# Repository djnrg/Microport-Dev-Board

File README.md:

# Microport-Dev-Board
Microport development board fot following microcontrollers:
* SAM D21
* PIC18F21

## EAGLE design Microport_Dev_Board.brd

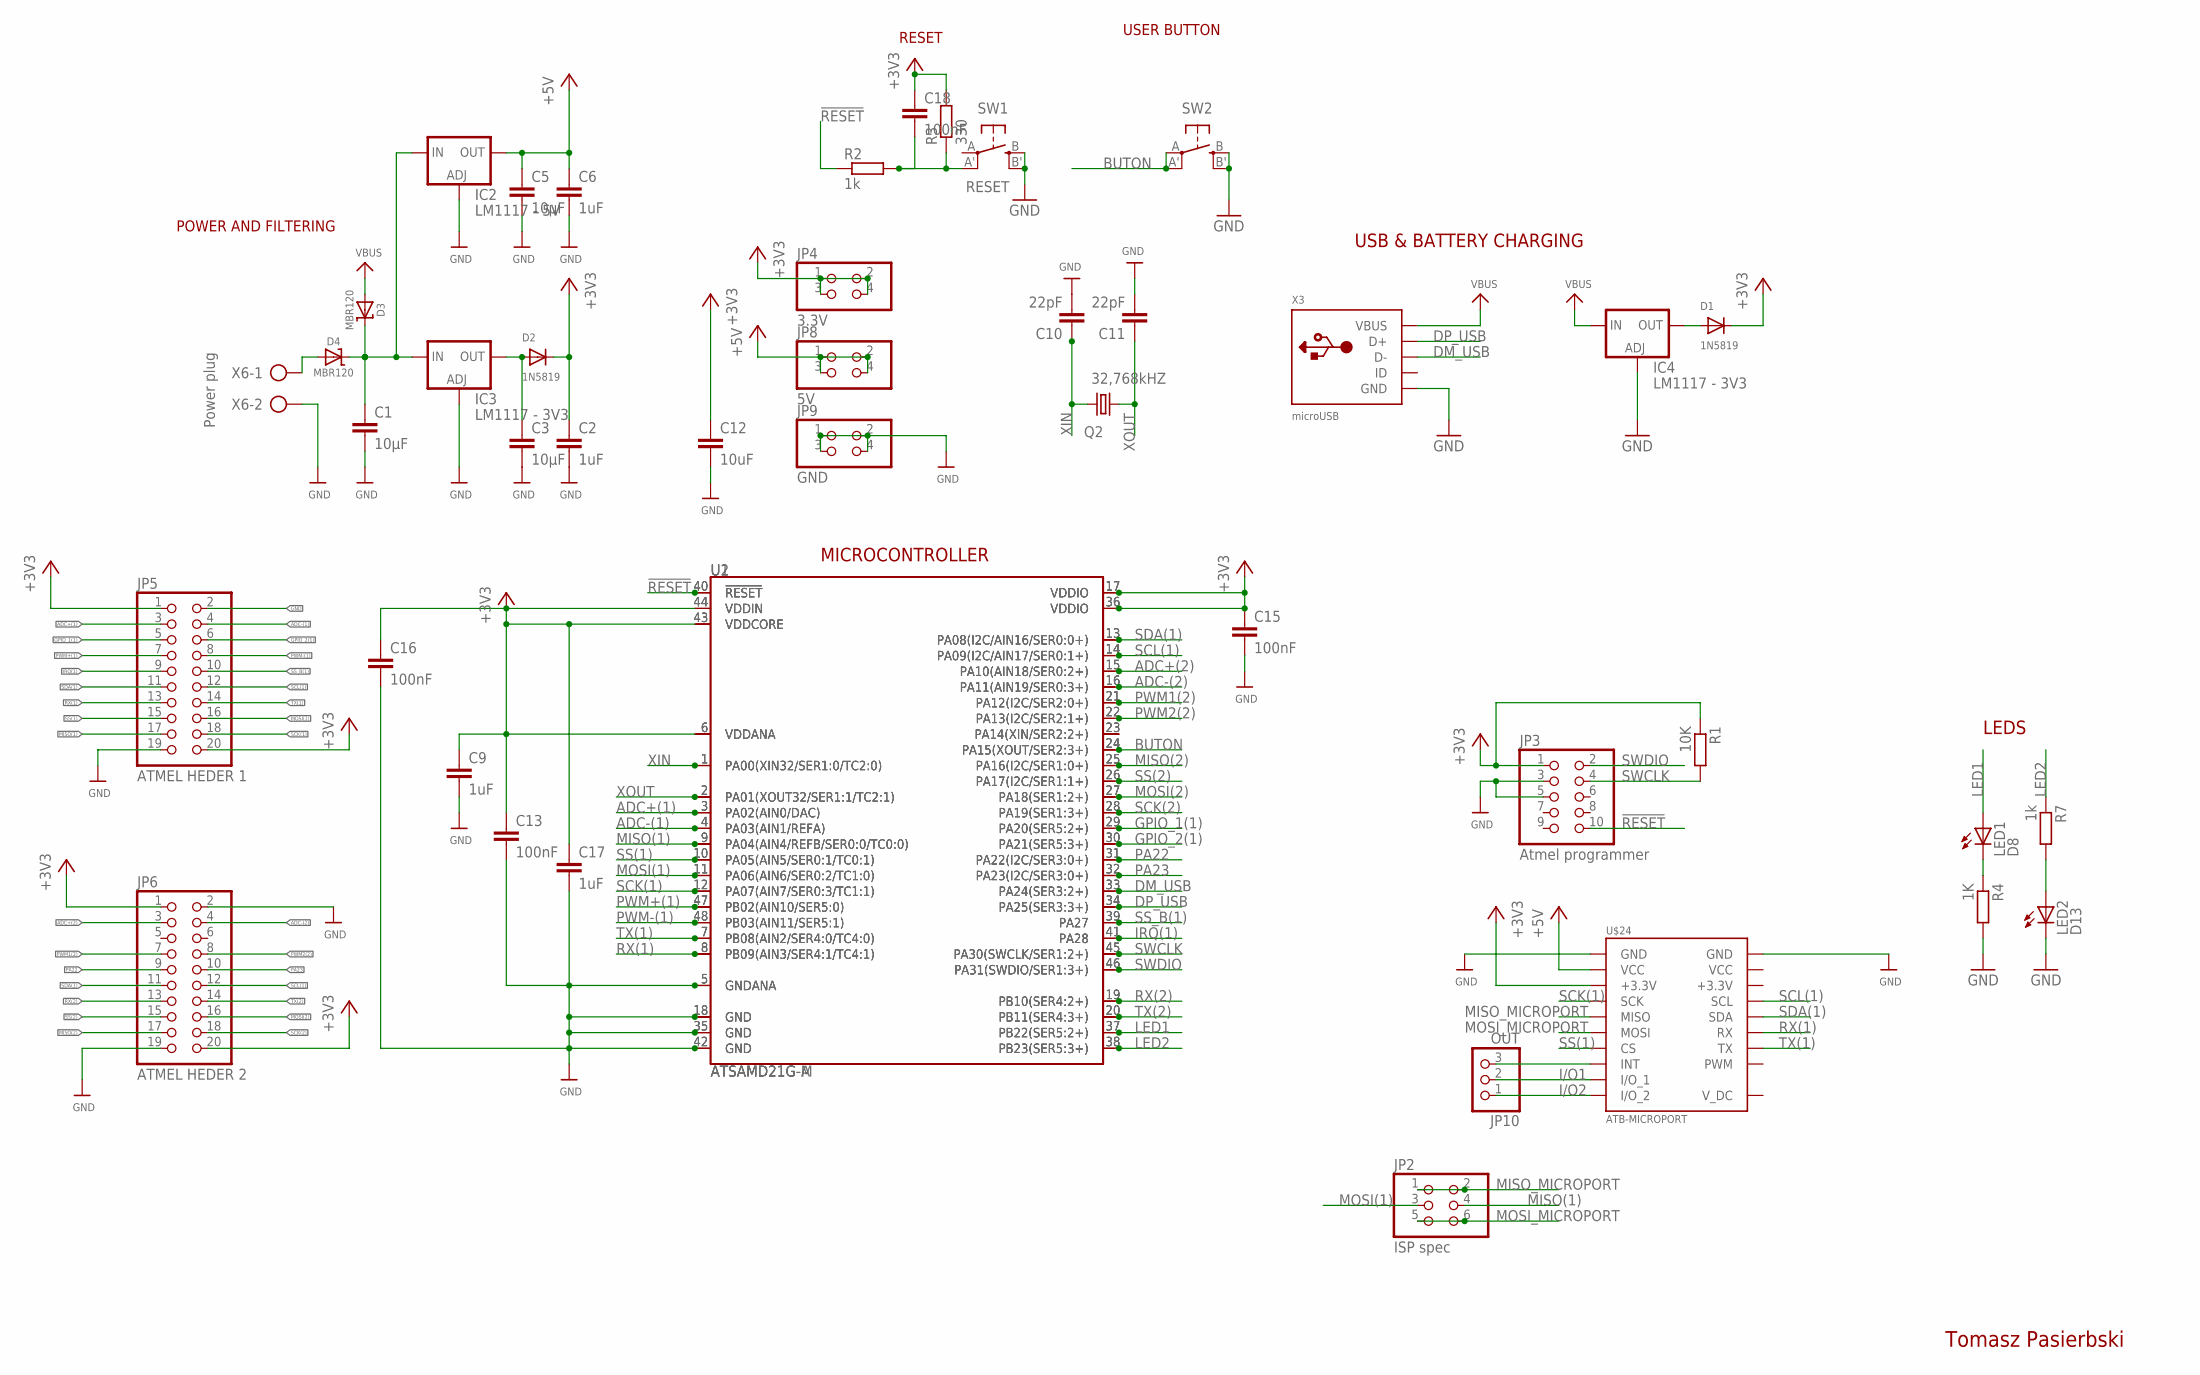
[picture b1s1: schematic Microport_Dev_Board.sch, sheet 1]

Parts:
C1, C3, C5: 10µF; C1206
C2, C6, C9, C17: 1uF; C1206
C10, C11: 22pF; C1206
C12: 10uF; C1206
C13, C15, C16, C18: 100nF; C1206
D1, D2: 1N5819; SOD-523
D3, D4: MBR120; SOD-123
IC2: LM1117 - 5V; SOT223
IC3, IC4: LM1117 - 3V3; SOT223
JP2: ISP spec; 2X03
JP3: Atmel programmer; 2X05
JP4: 3.3V; 2X02
JP5: ATMEL HEDER 1; 2X10
JP6: ATMEL HEDER 2; 2X10
JP8: 5V; 2X02
JP9: GND; 2X02
JP10: OUT; 1X03
LED1: D8; 1206
LED2: D13; 1206
Q2: 32,768kHZ; HC49UP
R1: 10K; M1206
R2: 1k; R1206
R3: 330; R1206
R4: 1K; M1206
R7: 1k; M1206
SW1: RESET; EVQ-Q2
SW2: USER BUTTON; EVQ-Q2
U1: ATSAMD21G-M; QFN-48
U2: ATSAMD21G-A; TQFP-48
U$24: ATB-MICROPORT
X3: microUSB; USB-MINIB
X6: Power plug; AK300/2

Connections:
!RESET: JP3.10, R2.1, U1.40 (!RESET!), U2.40 (!RESET!); also elsewhere on the board
+3.3V: U$24.P$17 (+3.3V)
+3V3: C2.1, C9.1, C12.1, C13.1, C15.1, C16.1, C17.1, C18.1, D1.K (C), D2.K (C), JP3.1, JP4.1, JP4.2, JP4.3, JP4.4, JP5.1, JP5.20, JP6.1, JP6.20, R1.1, R3.2, U1.17 (VDDIO), U1.36 (VDDIO), U2.6 (VDDANA), U2.17 (VDDIO), U2.36 (VDDIO), U2.43 (VDDCORE), U2.44 (VDDIN), U$24.P$3 (+3.3V); also elsewhere on the board
+5V: C5.1, C6.1, IC2.4 (OUT), JP8.1, JP8.2, JP8.3, JP8.4, U$24.P$2 (VCC); also elsewhere on the board
ADC+(1): JP5.3, U1.3 (PA02(AIN0/DAC)), U2.3 (PA02(AIN0/DAC))
ADC+(2): JP6.3, U1.15 (PA10(AIN18/SER0:2+)), U2.15 (PA10(AIN18/SER0:2+))
ADC-(1): JP5.4, U1.4 (PA03(AIN1/REFA)), U2.4 (PA03(AIN1/REFA))
ADC-(2): JP6.4, U1.16 (PA11(AIN19/SER0:3+)), U2.16 (PA11(AIN19/SER0:3+))
BUTON: SW2.A, SW2.A' (P1), U1.24 (PA15(XOUT/SER2:3+)), U2.24 (PA15(XOUT/SER2:3+))
DM_USB: U1.33 (PA24(SER3:2+)), U2.33 (PA24(SER3:2+)), X3.D-; also elsewhere on the board
DP_USB: U1.34 (PA25(SER3:3+)), U2.34 (PA25(SER3:3+)), X3.D+; also elsewhere on the board
GND: C1.2, C2.2, C3.2, C5.2, C6.2, C9.2, C10.2, C11.2, C12.2, C13.2, C15.2, C16.2, C17.2, IC2.1 (ADJ), IC3.1 (ADJ), IC4.1 (ADJ), JP3.3, JP3.5, JP5.2, JP5.19, JP6.2, JP6.19, JP9.1, JP9.2, JP9.3, JP9.4, LED2.C, R4.2, SW1.B (S), SW1.B' (S1), SW2.B (S), SW2.B' (S1), U1.5 (GNDANA), U1.18 (GND), U1.35 (GND), U1.42 (GND), U2.5 (GNDANA), U2.18 (GND), U2.35 (GND), U2.42 (GND), U$24.P$1 (GND), U$24.P$19 (GND), X3.GND, X6.2; also elsewhere on the board
GPIO_1(1): JP5.5, U1.29 (PA20(SER5:2+)), U2.29 (PA20(SER5:2+))
GPIO_2(1): JP5.6, U1.30 (PA21(SER5:3+)), U2.30 (PA21(SER5:3+))
I/O1: JP10.2, U$24.P$9 (I/O_1)
I/O2: JP10.1, U$24.P$10 (I/O_2)
IRQ(1): JP5.9, U1.41 (PA28), U2.41 (PA28)
LED1: LED1.A, U1.37 (PB22(SER5:2+)), U2.37 (PB22(SER5:2+))
LED2: R7.1, U1.38 (PB23(SER5:3+)), U2.38 (PB23(SER5:3+))
MISO(1): JP2.4, JP5.17, U1.9 (PA04(AIN4/REFB/SER0:0/TC0:0)), U2.9 (PA04(AIN4/REFB/SER0:0/TC0:0))
MISO(2): JP6.17, U1.25 (PA16(I2C/SER1:0+)), U2.25 (PA16(I2C/SER1:0+))
MISO_MICROPORT: JP2.1, JP2.2, U$24.P$5 (MISO)
MOSI(1): JP2.3, JP5.16, U1.11 (PA06(AIN6/SER0:2/TC1:0)), U2.11 (PA06(AIN6/SER0:2/TC1:0))
MOSI(2): JP6.16, U1.27 (PA18(SER1:2+)), U2.27 (PA18(SER1:2+))
MOSI_MICROPORT: JP2.5, JP2.6, U$24.P$6 (MOSI)
unnamed: LED2.A, R7.2
unnamed: C1.1, D3.C, D4.C, IC2.3 (IN), IC3.3 (IN)
unnamed: D1.A, IC4.4 (OUT)
unnamed: LED1.C, R4.1
unnamed: D4.A, X6.1
unnamed: C3.1, D2.A, IC3.4 (OUT)
unnamed: C18.2, R2.2, R3.1, SW1.A' (P1)
unnamed: JP10.3, U$24.P$8 (INT)
unnamed: U1.23 (PA14(XIN/SER2:2+)), U2.23 (PA14(XIN/SER2:2+))
PA22: JP6.9, U1.31 (PA22(I2C/SER3:0+)), U2.31 (PA22(I2C/SER3:0+))
PA23: JP6.10, U1.32 (PA23(I2C/SER3:0+)), U2.32 (PA23(I2C/SER3:0+))
PWM1(2): JP6.7, U1.21 (PA12(I2C/SER2:0+)), U2.21 (PA12(I2C/SER2:0+))
PWM2(2): JP6.8, U1.22 (PA13(I2C/SER2:1+)), U2.22 (PA13(I2C/SER2:1+))
PWM+(1): JP5.7, U1.47 (PB02(AIN10/SER5:0)), U2.47 (PB02(AIN10/SER5:0))
PWM-(1): JP5.8, U1.48 (PB03(AIN11/SER5:1)), U2.48 (PB03(AIN11/SER5:1))
RX(1): JP5.13, U1.8 (PB09(AIN3/SER4:1/TC4:1)), U2.8 (PB09(AIN3/SER4:1/TC4:1)), U$24.P$14 (RX); also elsewhere on the board
RX(2): JP6.13, U1.19 (PB10(SER4:2+)), U2.19 (PB10(SER4:2+))
SCK(1): JP5.18, U1.12 (PA07(AIN7/SER0:3/TC1:1)), U2.12 (PA07(AIN7/SER0:3/TC1:1)), U$24.P$4 (SCK)
SCK(2): JP6.18, U1.28 (PA19(SER1:3+)), U2.28 (PA19(SER1:3+))
SCL(1): JP5.12, JP6.12, U1.14 (PA09(I2C/AIN17/SER0:1+)), U2.14 (PA09(I2C/AIN17/SER0:1+)), U$24.P$16 (SCL); also elsewhere on the board
SDA(1): JP5.11, JP6.11, U1.13 (PA08(I2C/AIN16/SER0:0+)), U2.13 (PA08(I2C/AIN16/SER0:0+)), U$24.P$15 (SDA); also elsewhere on the board
SS(1): JP5.15, U1.10 (PA05(AIN5/SER0:1/TC0:1)), U2.10 (PA05(AIN5/SER0:1/TC0:1)), U$24.P$7 (CS)
SS(2): JP6.15, U1.26 (PA17(I2C/SER1:1+)), U2.26 (PA17(I2C/SER1:1+))
SS_B(1): JP5.10, U1.39 (PA27), U2.39 (PA27)
SWCLK: JP3.4, R1.2, U1.45 (PA30(SWCLK/SER1:2+)), U2.45 (PA30(SWCLK/SER1:2+))
SWDIO: JP3.2, U1.46 (PA31(SWDIO/SER1:3+)), U2.46 (PA31(SWDIO/SER1:3+))
TX(1): JP5.14, U1.7 (PB08(AIN2/SER4:0/TC4:0)), U2.7 (PB08(AIN2/SER4:0/TC4:0)), U$24.P$13 (TX); also elsewhere on the board
TX(2): JP6.14, U1.20 (PB11(SER4:3+)), U2.20 (PB11(SER4:3+))
VBUS: D3.A, IC4.3 (IN), X3.VBUS; also elsewhere on the board
VCC: U$24.P$18 (VCC)
V_DC: U$24.P$11 (V_DC)
XIN: C10.1, Q2.2, U1.1 (PA00(XIN32/SER1:0/TC2:0)), U2.1 (PA00(XIN32/SER1:0/TC2:0))
XOUT: C11.1, Q2.1, U1.2 (PA01(XOUT32/SER1:1/TC2:1)), U2.2 (PA01(XOUT32/SER1:1/TC2:1))

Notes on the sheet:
POWER AND FILTERING
RESET
USB & BATTERY CHARGING
LEDS
MICROCONTROLLER
Tomasz Pasierbski

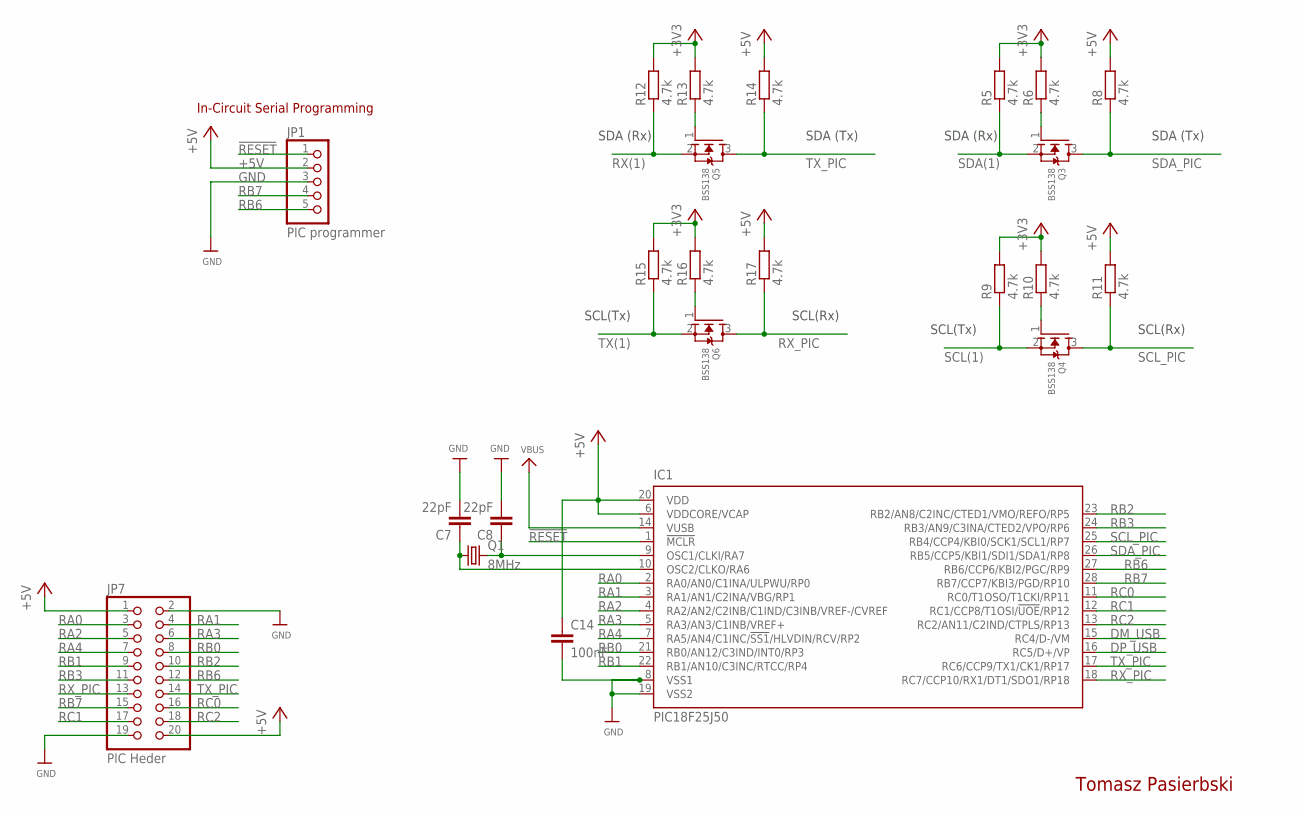
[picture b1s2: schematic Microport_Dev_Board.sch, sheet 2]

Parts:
C7, C8: 22pF; C1206
C14: 100nF; C1206
IC1: PIC18F25J50; DIL28-3
JP1: PIC programmer; 1X05
JP7: PIC Heder; 2X10
Q1: 8MHz; HC49/S
Q3, Q4, Q5, Q6: BSS138; SOT23-W
R5, R6, R8, R9, R10, R11, R12, R13, R14, R15, R16, R17: 4.7k; R1206

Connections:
!RESET: IC1.1 (!MCLR), JP1.1; also elsewhere on the board
+3V3: R5.2, R6.2, R9.2, R10.2, R12.2, R13.2, R15.2, R16.2; also elsewhere on the board
+5V: C14.1, IC1.6 (VDDCORE/VCAP), IC1.20 (VDD), JP1.2, JP7.1, JP7.20, R8.2, R11.2, R14.2, R17.2; also elsewhere on the board
DM_USB: IC1.15 (RC4/D-/VM); also elsewhere on the board
DP_USB: IC1.16 (RC5/D+/VP); also elsewhere on the board
GND: C7.2, C8.2, C14.2, IC1.8 (VSS1), IC1.19 (VSS2), JP1.3, JP7.2, JP7.19; also elsewhere on the board
unnamed: C8.1, IC1.9 (OSC1/CLKI/RA7), Q1.2
unnamed: C7.1, IC1.10 (OSC2/CLKO/RA6), Q1.1
unnamed: Q3.1 (G), R6.1
unnamed: Q4.1 (G), R10.1
unnamed: Q5.1 (G), R13.1
unnamed: Q6.1 (G), R16.1
RA0: IC1.2 (RA0/AN0/C1INA/ULPWU/RP0), JP7.3
RA1: IC1.3 (RA1/AN1/C2INA/VBG/RP1), JP7.4
RA2: IC1.4 (RA2/AN2/C2INB/C1IND/C3INB/VREF-/CVREF), JP7.5
RA3: IC1.5 (RA3/AN3/C1INB/VREF+), JP7.6
RA4: IC1.7 (RA5/AN4/C1INC/!SS1!/HLVDIN/RCV/RP2), JP7.7
RB0: IC1.21 (RB0/AN12/C3IND/INT0/RP3), JP7.8
RB1: IC1.22 (RB1/AN10/C3INC/RTCC/RP4), JP7.9
RB2: IC1.23 (RB2/AN8/C2INC/CTED1/VMO/REFO/RP5), JP7.10
RB3: IC1.24 (RB3/AN9/C3INA/CTED2/VPO/RP6), JP7.11
RB6: IC1.27 (RB6/CCP6/KBI2/PGC/RP9), JP1.5, JP7.12
RB7: IC1.28 (RB7/CCP7/KBI3/PGD/RP10), JP1.4, JP7.15
RC0: IC1.11 (RC0/T1OSO/T1CKI/RP11), JP7.16
RC1: IC1.12 (RC1/CCP8/T1OSI/!UOE!/RP12), JP7.17
RC2: IC1.13 (RC2/AN11/C2IND/CTPLS/RP13), JP7.18
RX(1): Q5.2 (S), R12.1; also elsewhere on the board
RX_PIC: IC1.18 (RC7/CCP10/RX1/DT1/SDO1/RP18), JP7.13, Q6.3 (D), R17.1
SCL(1): Q4.2 (S), R9.1; also elsewhere on the board
SCL_PIC: IC1.25 (RB4/CCP4/KBI0/SCK1/SCL1/RP7), Q4.3 (D), R11.1
SDA(1): Q3.2 (S), R5.1; also elsewhere on the board
SDA_PIC: IC1.26 (RB5/CCP5/KBI1/SDI1/SDA1/RP8), Q3.3 (D), R8.1
TX(1): Q6.2 (S), R15.1; also elsewhere on the board
TX_PIC: IC1.17 (RC6/CCP9/TX1/CK1/RP17), JP7.14, Q5.3 (D), R14.1
VBUS: IC1.14 (VUSB); also elsewhere on the board

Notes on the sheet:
In-Circuit Serial Programming
SDA (Rx)
SDA (Tx)
SCL(Tx)
SCL(Rx)
Tomasz Pasierbski

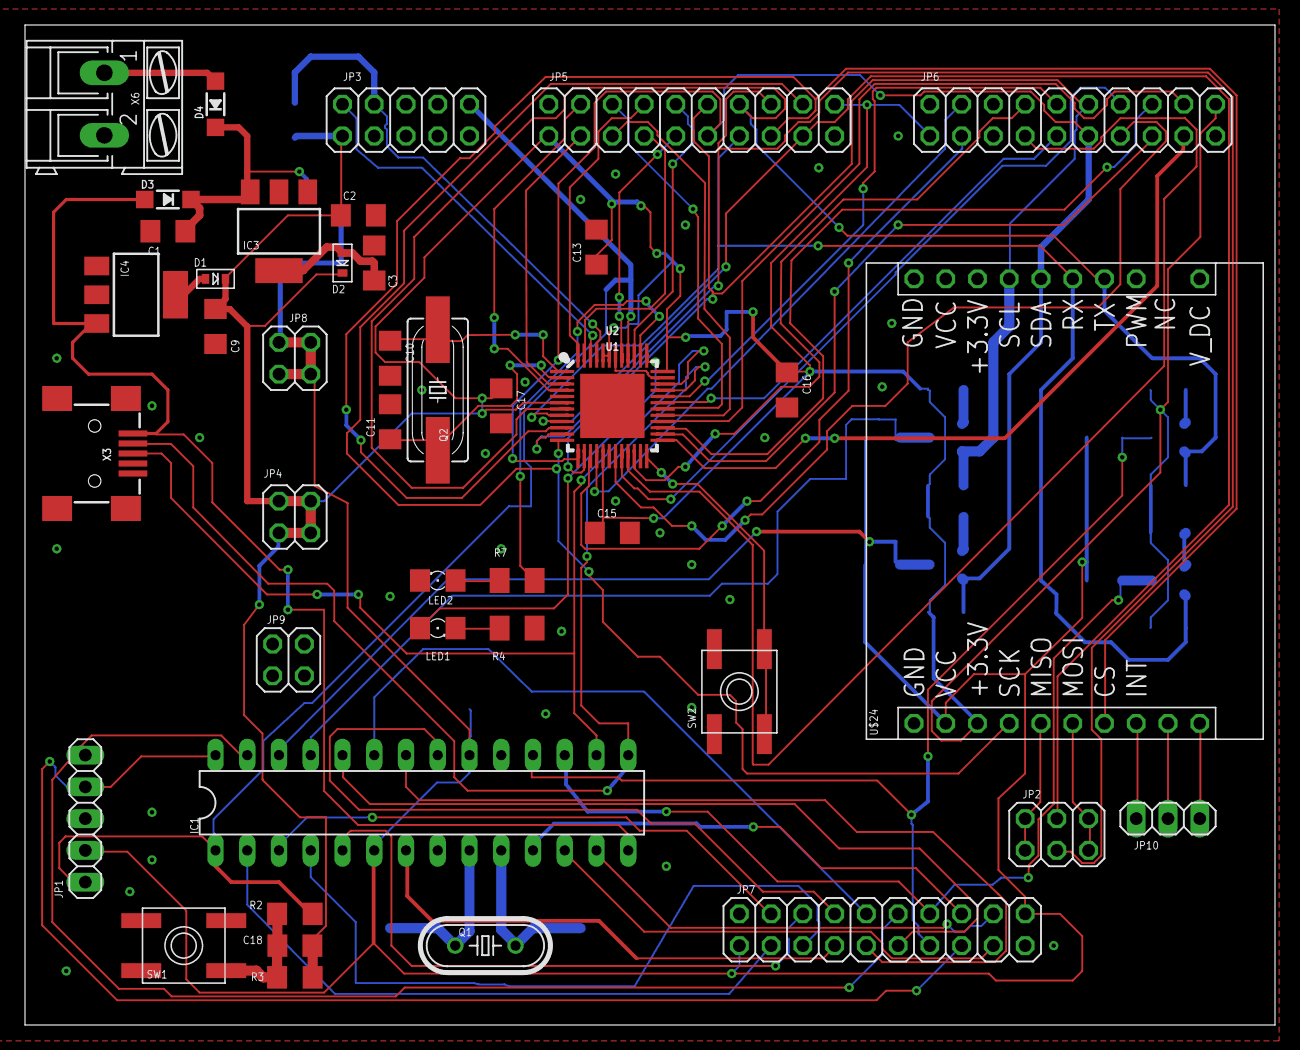
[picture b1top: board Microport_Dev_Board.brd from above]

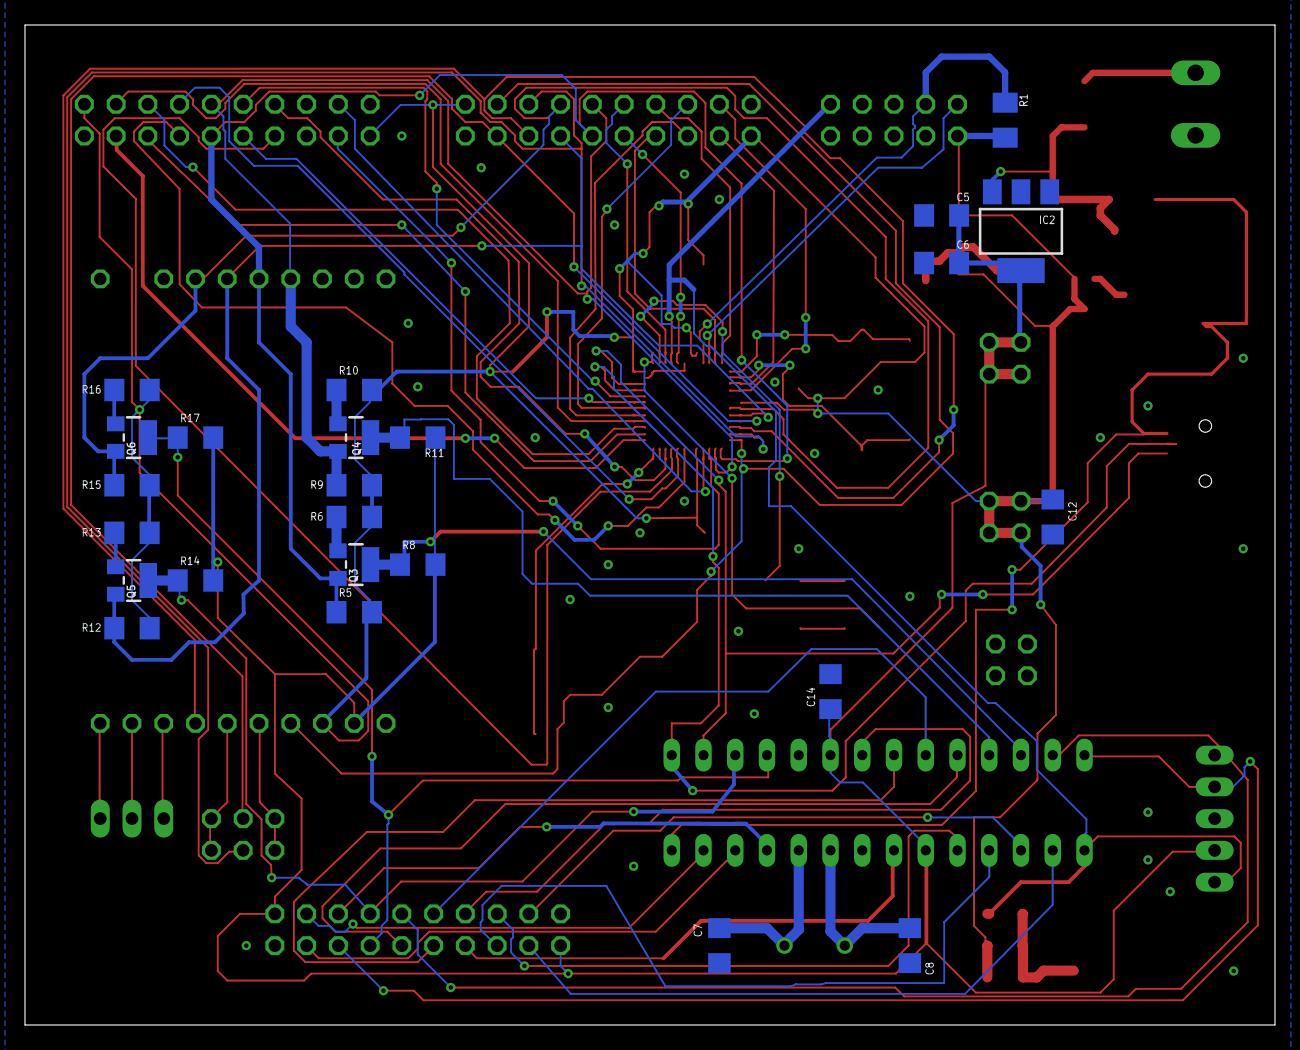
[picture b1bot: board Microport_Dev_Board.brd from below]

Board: 2 copper layers, 100.0 x 80.0 mm, 67 parts (24 on the bottom side), 79 nets.

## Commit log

2018-12-01 Upload initial file
    Uploaded last file before manufacturing
2018-12-01 Create LICENSE

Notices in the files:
parts and their libraries:
microbuilder: This work is placed in the public domain, and may be freely used for commercial and non-commercial work with the following conditions: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
SparkFun-IC-Microcontroller: Licensing: Creative Commons ShareAlike 4.0 International - https://creativecommons.org/licenses/by-sa/4.0
